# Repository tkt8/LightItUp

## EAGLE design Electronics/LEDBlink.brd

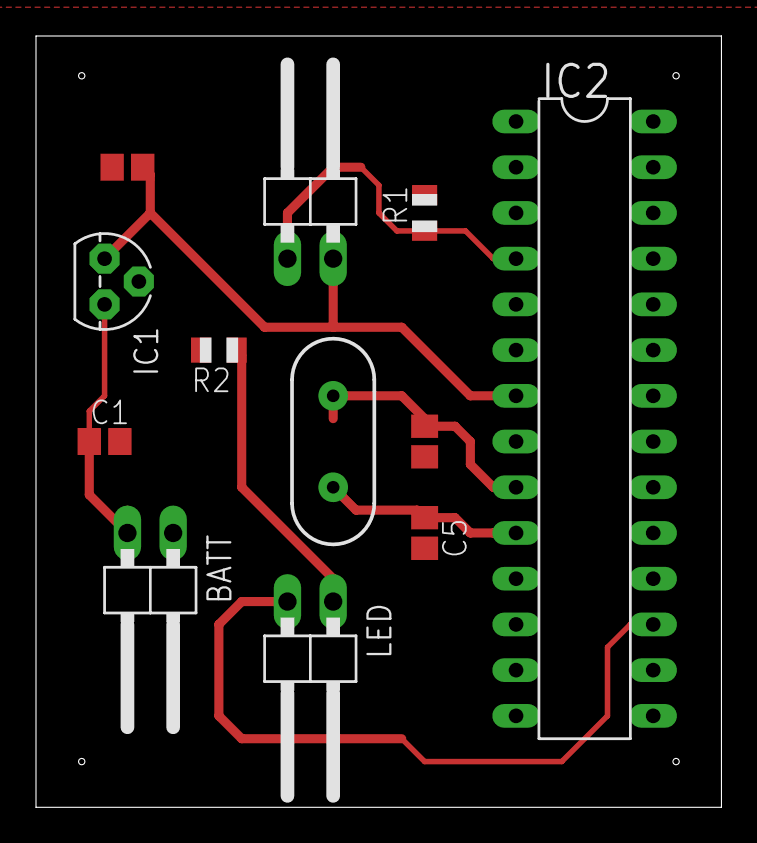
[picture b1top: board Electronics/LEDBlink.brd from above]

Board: 2 copper layers, 38.1 x 42.8 mm, 12 parts (0 on the bottom side), 8 nets.

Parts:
BATT: 1X02/90
BUTTON: 1X02/90
C1: 0.47uF; C0805
C2: 0.1uF; C0805
C3, C5: 22pF; C0805
IC1: 7805L; TO92
IC2: ATMEGA328-20P; DIL28-3
LED: RED; 1X02/90
R1: 20k; R0805
R2: 150; R0805
Y1: 16MHz; HC49US

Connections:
+5V: BUTTON.2, C2.1, IC1.1, IC2.7
BATT: BATT.2, C1.1, IC1.3
GND: BATT.1, C1.2, C2.2, C3.2, C5.2, IC1.2, IC2.8, R1.2, R2.2
unnamed: C3.1, IC2.9, Y1.1
unnamed: LED.1, R2.1
unnamed: C5.1, IC2.10, Y1.2
PWM_PIN: IC2.17, LED.2
SWN: BUTTON.1, IC2.4, R1.1

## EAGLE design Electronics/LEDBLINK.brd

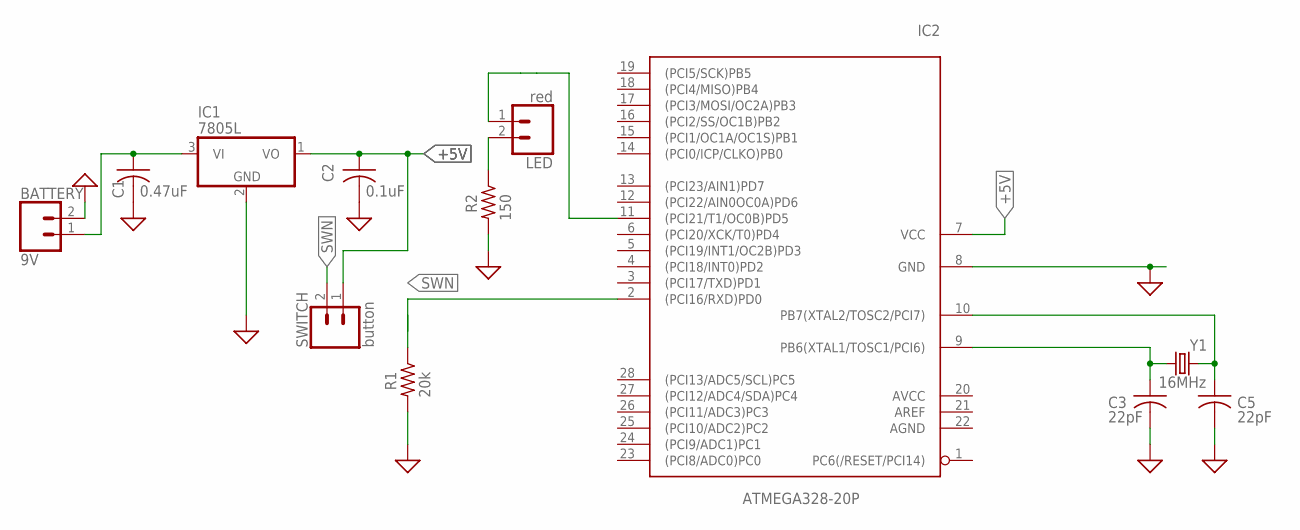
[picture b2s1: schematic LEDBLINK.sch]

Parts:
BATTERY: 9V; 1X02
C1: 0.47uF; C0805
C2: 0.1uF; C0805
C3, C5: 22pF; C0805
IC1: 7805L; TO92
IC2: ATMEGA328-20P; DIL28-3
LED: red; 1X02
R1: 20k; R0805
R2: 150; R0805
SWITCH: button; 1X02
Y1: 16MHz; HC49US

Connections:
+5V: C2.1, IC1.1 (VO), IC2.7 (VCC), SWITCH.1
GND: BATTERY.2, C1.2, C2.2, C3.2, C5.2, IC1.2 (GND), IC2.8 (GND), R1.2, R2.2
unnamed: C3.1, IC2.9 (PB6(XTAL1/TOSC1/PCI6)), Y1.1
unnamed: BATTERY.1, C1.1, IC1.3 (VI)
unnamed: LED.2, R2.1
unnamed: C5.1, IC2.10 (PB7(XTAL2/TOSC2/PCI7)), Y1.2
PWM_PIN: IC2.11 ((PCI21/T1/OC0B)PD5), LED.1
SWN: IC2.2 ((PCI16/RXD)PD0), R1.1, SWITCH.2

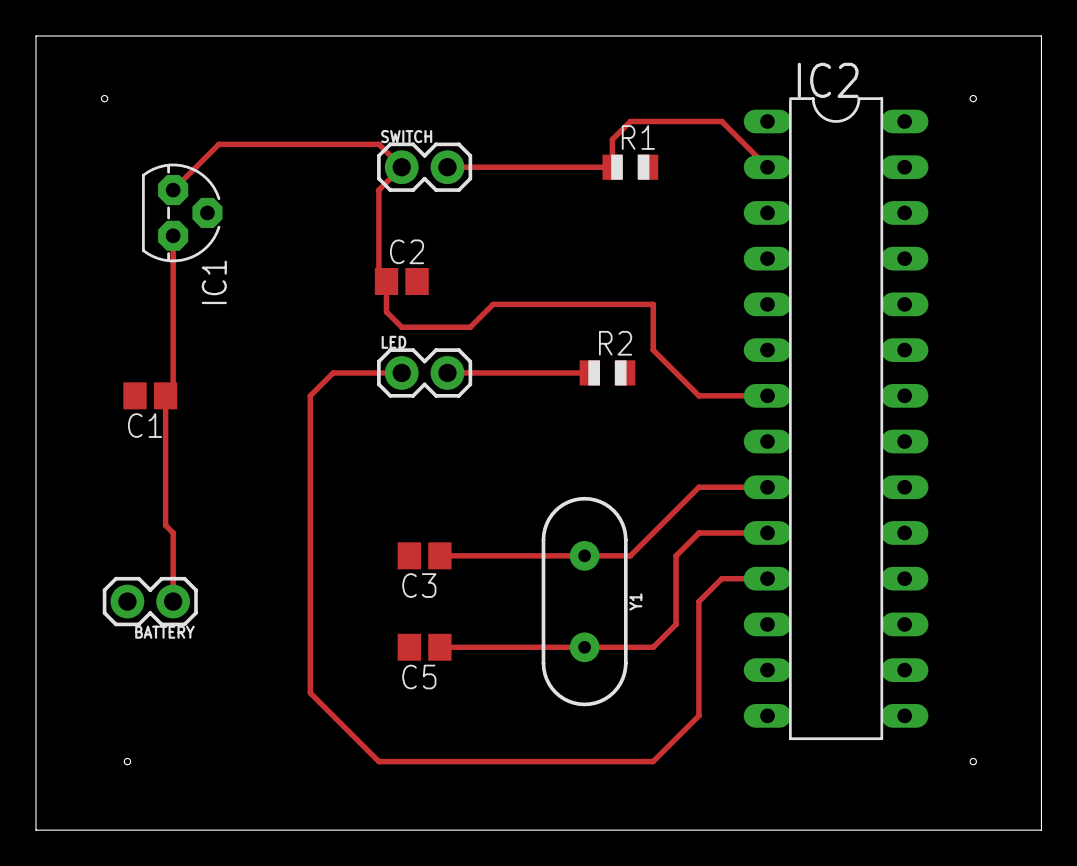
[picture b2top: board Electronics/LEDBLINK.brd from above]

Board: 2 copper layers, 55.9 x 44.1 mm, 12 parts (0 on the bottom side), 8 nets.

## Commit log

2018-10-02 Creating new Directories
2018-11-01 Adding Schematics
2018-11-06 Adding psuedocode (closes #17)
2018-11-06 Updating psuedoCode and adding Flowchart
2018-11-08 Adding schematic
2018-11-08 Adding schematic 2
2018-11-19 updated schematics and pcb added
2018-11-19 updated pcb
2018-12-01 Uploading code
2018-12-14 Code final
2018-12-14 mech design
2019-09-02 Created using Colaboratory

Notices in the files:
parts and their libraries:
SparkFun-Connectors: Licensing: Creative Commons ShareAlike 4.0 International - https://creativecommons.org/licenses/by-sa/4.0
